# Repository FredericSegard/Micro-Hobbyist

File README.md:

# Micro-Hobbyist
 Frederic's electronics hobby repository

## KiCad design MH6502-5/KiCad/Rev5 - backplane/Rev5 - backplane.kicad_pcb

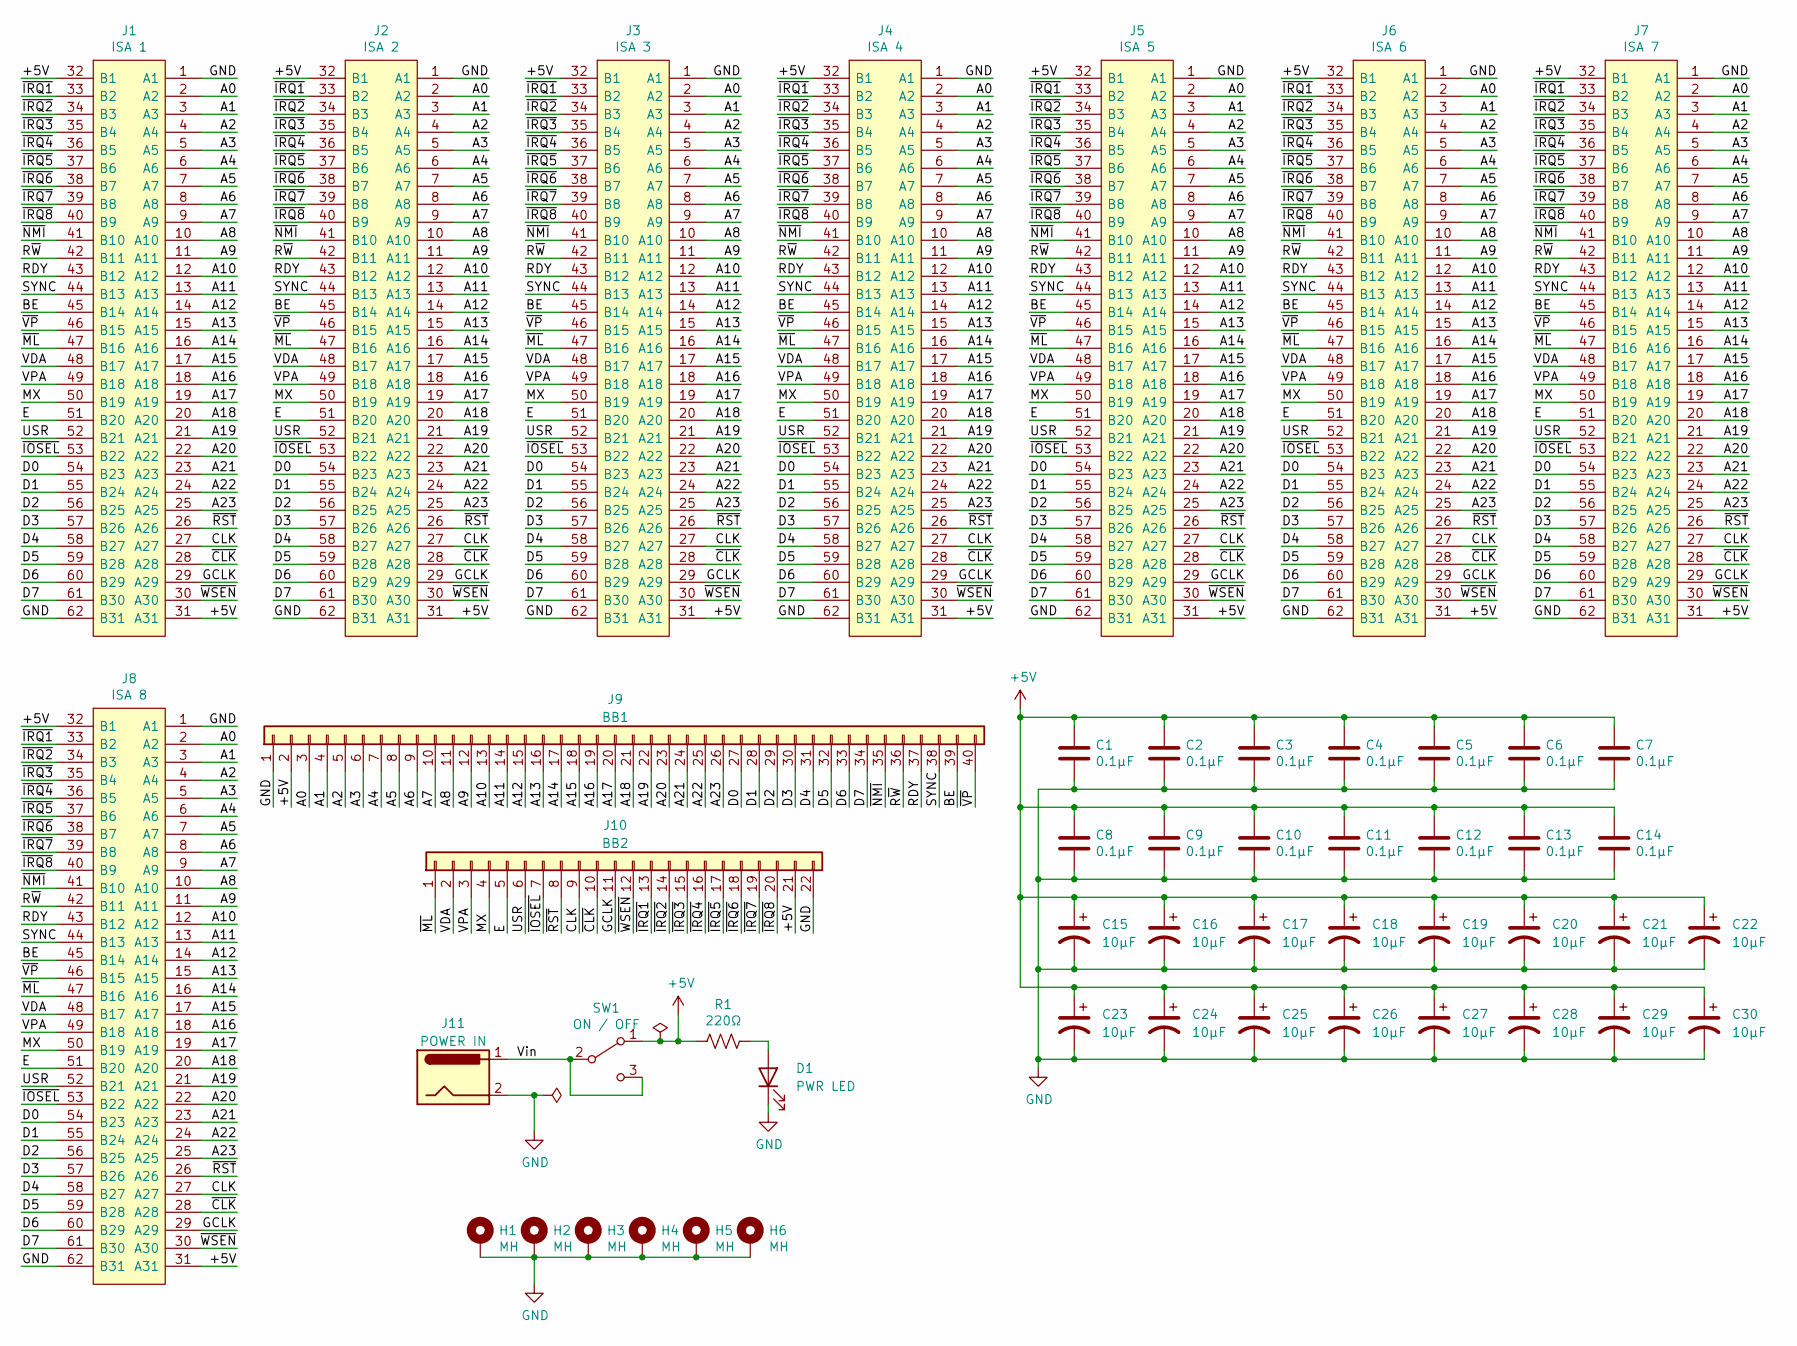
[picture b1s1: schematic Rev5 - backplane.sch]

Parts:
C1, C2, C3, C4, C5, C6, C7, C8, C9, C10, C11, C12, C13, C14: 0.1µF; C_Disc_D3.0mm_W2.0mm_P2.50mm
C15, C16, C17, C18, C19, C20, C21, C22, C23, C24, C25, C26, C27, C28, C29, C30: 10µF; CP_Radial_D6.3mm_P2.50mm
D1: PWR LED; LED_D3.0mm
H1, H2, H3, H4, H5, H6: MH; MountingHole_3.2mm_M3_Pad_Via
J1: ISA 1; ISA_Connector; Mouser Part Number 571-6-5530843-5
J2: ISA 2; ISA_Connector; Mouser Part Number 571-6-5530843-5
J3: ISA 3; ISA_Connector; Mouser Part Number 571-6-5530843-5
J4: ISA 4; ISA_Connector; Mouser Part Number 571-6-5530843-5
J5: ISA 5; ISA_Connector; Mouser Part Number 571-6-5530843-5
J6: ISA 6; ISA_Connector; Mouser Part Number 571-6-5530843-5
J7: ISA 7; ISA_Connector; Mouser Part Number 571-6-5530843-5
J8: ISA 8; ISA_Connector; Mouser Part Number 571-6-5530843-5
J9: BB1; PinHeader_1x40_P2.54mm_Vertical
J10: BB2; PinHeader_1x22_P2.54mm_Vertical
J11: POWER IN; BarrelJack_Horizontal
R1: 220Ω; R_Axial_DIN0207_L6.3mm_D2.5mm_P10.16mm_Horizontal
SW1: ON / OFF; Microswitch_3mm_spacing

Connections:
+5V: C1.1, C2.1, C3.1, C4.1, C5.1, C6.1, C7.1, C8.1, C9.1, C10.1, C11.1, C12.1, C13.1, C14.1, C15.1, C16.1, C17.1, C18.1, C19.1, C20.1, C21.1, C22.1, C23.1, C24.1, C25.1, C26.1, C27.1, C28.1, C29.1, C30.1, J1.31 (A31), J1.32 (B1), J2.31 (A31), J2.32 (B1), J3.31 (A31), J3.32 (B1), J4.31 (A31), J4.32 (B1), J5.31 (A31), J5.32 (B1), J6.31 (A31), J6.32 (B1), J7.31 (A31), J7.32 (B1), J8.31 (A31), J8.32 (B1), J9.2, J10.21, R1.2, SW1.1 (A)
/A0: J1.2 (A2), J2.2 (A2), J3.2 (A2), J4.2 (A2), J5.2 (A2), J6.2 (A2), J7.2 (A2), J8.2 (A2), J9.3
/A1: J1.3 (A3), J2.3 (A3), J3.3 (A3), J4.3 (A3), J5.3 (A3), J6.3 (A3), J7.3 (A3), J8.3 (A3), J9.4
/A2: J1.4 (A4), J2.4 (A4), J3.4 (A4), J4.4 (A4), J5.4 (A4), J6.4 (A4), J7.4 (A4), J8.4 (A4), J9.5
/A3: J1.5 (A5), J2.5 (A5), J3.5 (A5), J4.5 (A5), J5.5 (A5), J6.5 (A5), J7.5 (A5), J8.5 (A5), J9.6
/A4: J1.6 (A6), J2.6 (A6), J3.6 (A6), J4.6 (A6), J5.6 (A6), J6.6 (A6), J7.6 (A6), J8.6 (A6), J9.7
/A5: J1.7 (A7), J2.7 (A7), J3.7 (A7), J4.7 (A7), J5.7 (A7), J6.7 (A7), J7.7 (A7), J8.7 (A7), J9.8
/A6: J1.8 (A8), J2.8 (A8), J3.8 (A8), J4.8 (A8), J5.8 (A8), J6.8 (A8), J7.8 (A8), J8.8 (A8), J9.9
/A7: J1.9 (A9), J2.9 (A9), J3.9 (A9), J4.9 (A9), J5.9 (A9), J6.9 (A9), J7.9 (A9), J8.9 (A9), J9.10
/A8: J1.10 (A10), J2.10 (A10), J3.10 (A10), J4.10 (A10), J5.10 (A10), J6.10 (A10), J7.10 (A10), J8.10 (A10), J9.11
/A9: J1.11 (A11), J2.11 (A11), J3.11 (A11), J4.11 (A11), J5.11 (A11), J6.11 (A11), J7.11 (A11), J8.11 (A11), J9.12
/A10: J1.12 (A12), J2.12 (A12), J3.12 (A12), J4.12 (A12), J5.12 (A12), J6.12 (A12), J7.12 (A12), J8.12 (A12), J9.13
/A11: J1.13 (A13), J2.13 (A13), J3.13 (A13), J4.13 (A13), J5.13 (A13), J6.13 (A13), J7.13 (A13), J8.13 (A13), J9.14
/A12: J1.14 (A14), J2.14 (A14), J3.14 (A14), J4.14 (A14), J5.14 (A14), J6.14 (A14), J7.14 (A14), J8.14 (A14), J9.15
/A13: J1.15 (A15), J2.15 (A15), J3.15 (A15), J4.15 (A15), J5.15 (A15), J6.15 (A15), J7.15 (A15), J8.15 (A15), J9.16
/A14: J1.16 (A16), J2.16 (A16), J3.16 (A16), J4.16 (A16), J5.16 (A16), J6.16 (A16), J7.16 (A16), J8.16 (A16), J9.17
/A15: J1.17 (A17), J2.17 (A17), J3.17 (A17), J4.17 (A17), J5.17 (A17), J6.17 (A17), J7.17 (A17), J8.17 (A17), J9.18
/A16: J1.18 (A18), J2.18 (A18), J3.18 (A18), J4.18 (A18), J5.18 (A18), J6.18 (A18), J7.18 (A18), J8.18 (A18), J9.19
/A17: J1.19 (A19), J2.19 (A19), J3.19 (A19), J4.19 (A19), J5.19 (A19), J6.19 (A19), J7.19 (A19), J8.19 (A19), J9.20
/A18: J1.20 (A20), J2.20 (A20), J3.20 (A20), J4.20 (A20), J5.20 (A20), J6.20 (A20), J7.20 (A20), J8.20 (A20), J9.21
/A19: J1.21 (A21), J2.21 (A21), J3.21 (A21), J4.21 (A21), J5.21 (A21), J6.21 (A21), J7.21 (A21), J8.21 (A21), J9.22
/A20: J1.22 (A22), J2.22 (A22), J3.22 (A22), J4.22 (A22), J5.22 (A22), J6.22 (A22), J7.22 (A22), J8.22 (A22), J9.23
/A21: J1.23 (A23), J2.23 (A23), J3.23 (A23), J4.23 (A23), J5.23 (A23), J6.23 (A23), J7.23 (A23), J8.23 (A23), J9.24
/A22: J1.24 (A24), J2.24 (A24), J3.24 (A24), J4.24 (A24), J5.24 (A24), J6.24 (A24), J7.24 (A24), J8.24 (A24), J9.25
/A23: J1.25 (A25), J2.25 (A25), J3.25 (A25), J4.25 (A25), J5.25 (A25), J6.25 (A25), J7.25 (A25), J8.25 (A25), J9.26
/BE: J1.45 (B14), J2.45 (B14), J3.45 (B14), J4.45 (B14), J5.45 (B14), J6.45 (B14), J7.45 (B14), J8.45 (B14), J9.39
/CLK: J1.27 (A27), J2.27 (A27), J3.27 (A27), J4.27 (A27), J5.27 (A27), J6.27 (A27), J7.27 (A27), J8.27 (A27), J10.9
/D0: J1.54 (B23), J2.54 (B23), J3.54 (B23), J4.54 (B23), J5.54 (B23), J6.54 (B23), J7.54 (B23), J8.54 (B23), J9.27
/D1: J1.55 (B24), J2.55 (B24), J3.55 (B24), J4.55 (B24), J5.55 (B24), J6.55 (B24), J7.55 (B24), J8.55 (B24), J9.28
/D2: J1.56 (B25), J2.56 (B25), J3.56 (B25), J4.56 (B25), J5.56 (B25), J6.56 (B25), J7.56 (B25), J8.56 (B25), J9.29
/D3: J1.57 (B26), J2.57 (B26), J3.57 (B26), J4.57 (B26), J5.57 (B26), J6.57 (B26), J7.57 (B26), J8.57 (B26), J9.30
/D4: J1.58 (B27), J2.58 (B27), J3.58 (B27), J4.58 (B27), J5.58 (B27), J6.58 (B27), J7.58 (B27), J8.58 (B27), J9.31
/D5: J1.59 (B28), J2.59 (B28), J3.59 (B28), J4.59 (B28), J5.59 (B28), J6.59 (B28), J7.59 (B28), J8.59 (B28), J9.32
/D6: J1.60 (B29), J2.60 (B29), J3.60 (B29), J4.60 (B29), J5.60 (B29), J6.60 (B29), J7.60 (B29), J8.60 (B29), J9.33
/D7: J1.61 (B30), J2.61 (B30), J3.61 (B30), J4.61 (B30), J5.61 (B30), J6.61 (B30), J7.61 (B30), J8.61 (B30), J9.34
/E: J1.51 (B20), J2.51 (B20), J3.51 (B20), J4.51 (B20), J5.51 (B20), J6.51 (B20), J7.51 (B20), J8.51 (B20), J10.5
/GCLK: J1.29 (A29), J2.29 (A29), J3.29 (A29), J4.29 (A29), J5.29 (A29), J6.29 (A29), J7.29 (A29), J8.29 (A29), J10.11
/MX: J1.50 (B19), J2.50 (B19), J3.50 (B19), J4.50 (B19), J5.50 (B19), J6.50 (B19), J7.50 (B19), J8.50 (B19), J10.4
/RDY: J1.43 (B12), J2.43 (B12), J3.43 (B12), J4.43 (B12), J5.43 (B12), J6.43 (B12), J7.43 (B12), J8.43 (B12), J9.37
/R~W: J1.42 (B11), J2.42 (B11), J3.42 (B11), J4.42 (B11), J5.42 (B11), J6.42 (B11), J7.42 (B11), J8.42 (B11), J9.36
/SYNC: J1.44 (B13), J2.44 (B13), J3.44 (B13), J4.44 (B13), J5.44 (B13), J6.44 (B13), J7.44 (B13), J8.44 (B13), J9.38
/USR: J1.52 (B21), J2.52 (B21), J3.52 (B21), J4.52 (B21), J5.52 (B21), J6.52 (B21), J7.52 (B21), J8.52 (B21), J10.6
/VDA: J1.48 (B17), J2.48 (B17), J3.48 (B17), J4.48 (B17), J5.48 (B17), J6.48 (B17), J7.48 (B17), J8.48 (B17), J10.2
/VPA: J1.49 (B18), J2.49 (B18), J3.49 (B18), J4.49 (B18), J5.49 (B18), J6.49 (B18), J7.49 (B18), J8.49 (B18), J10.3
/Vin: J11.1, SW1.2 (B), SW1.3 (C)
/~CLK: J1.28 (A28), J2.28 (A28), J3.28 (A28), J4.28 (A28), J5.28 (A28), J6.28 (A28), J7.28 (A28), J8.28 (A28), J10.10
/~IOSEL: J1.53 (B22), J2.53 (B22), J3.53 (B22), J4.53 (B22), J5.53 (B22), J6.53 (B22), J7.53 (B22), J8.53 (B22), J10.7
/~IRQ1: J1.33 (B2), J2.33 (B2), J3.33 (B2), J4.33 (B2), J5.33 (B2), J6.33 (B2), J7.33 (B2), J8.33 (B2), J10.13
/~IRQ2: J1.34 (B3), J2.34 (B3), J3.34 (B3), J4.34 (B3), J5.34 (B3), J6.34 (B3), J7.34 (B3), J8.34 (B3), J10.14
/~IRQ3: J1.35 (B4), J2.35 (B4), J3.35 (B4), J4.35 (B4), J5.35 (B4), J6.35 (B4), J7.35 (B4), J8.35 (B4), J10.15
/~IRQ4: J1.36 (B5), J2.36 (B5), J3.36 (B5), J4.36 (B5), J5.36 (B5), J6.36 (B5), J7.36 (B5), J8.36 (B5), J10.16
/~IRQ5: J1.37 (B6), J2.37 (B6), J3.37 (B6), J4.37 (B6), J5.37 (B6), J6.37 (B6), J7.37 (B6), J8.37 (B6), J10.17
/~IRQ6: J1.38 (B7), J2.38 (B7), J3.38 (B7), J4.38 (B7), J5.38 (B7), J6.38 (B7), J7.38 (B7), J8.38 (B7), J10.18
/~IRQ7: J1.39 (B8), J2.39 (B8), J3.39 (B8), J4.39 (B8), J5.39 (B8), J6.39 (B8), J7.39 (B8), J8.39 (B8), J10.19
/~IRQ8: J1.40 (B9), J2.40 (B9), J3.40 (B9), J4.40 (B9), J5.40 (B9), J6.40 (B9), J7.40 (B9), J8.40 (B9), J10.20
/~ML: J1.47 (B16), J2.47 (B16), J3.47 (B16), J4.47 (B16), J5.47 (B16), J6.47 (B16), J7.47 (B16), J8.47 (B16), J10.1
/~NMI: J1.41 (B10), J2.41 (B10), J3.41 (B10), J4.41 (B10), J5.41 (B10), J6.41 (B10), J7.41 (B10), J8.41 (B10), J9.35
/~RST: J1.26 (A26), J2.26 (A26), J3.26 (A26), J4.26 (A26), J5.26 (A26), J6.26 (A26), J7.26 (A26), J8.26 (A26), J10.8
/~VP: J1.46 (B15), J2.46 (B15), J3.46 (B15), J4.46 (B15), J5.46 (B15), J6.46 (B15), J7.46 (B15), J8.46 (B15), J9.40
/~WSEN: J1.30 (A30), J2.30 (A30), J3.30 (A30), J4.30 (A30), J5.30 (A30), J6.30 (A30), J7.30 (A30), J8.30 (A30), J10.12
GND: C1.2, C2.2, C3.2, C4.2, C5.2, C6.2, C7.2, C8.2, C9.2, C10.2, C11.2, C12.2, C13.2, C14.2, C15.2, C16.2, C17.2, C18.2, C19.2, C20.2, C21.2, C22.2, C23.2, C24.2, C25.2, C26.2, C27.2, C28.2, C29.2, C30.2, D1.1 (K), H1.1, H2.1, H3.1, H4.1, H5.1, H6.1, J1.1 (A1), J1.62 (B31), J2.1 (A1), J2.62 (B31), J3.1 (A1), J3.62 (B31), J4.1 (A1), J4.62 (B31), J5.1 (A1), J5.62 (B31), J6.1 (A1), J6.62 (B31), J7.1 (A1), J7.62 (B31), J8.1 (A1), J8.62 (B31), J9.1, J10.22, J11.2
unnamed: D1.2 (A), R1.1

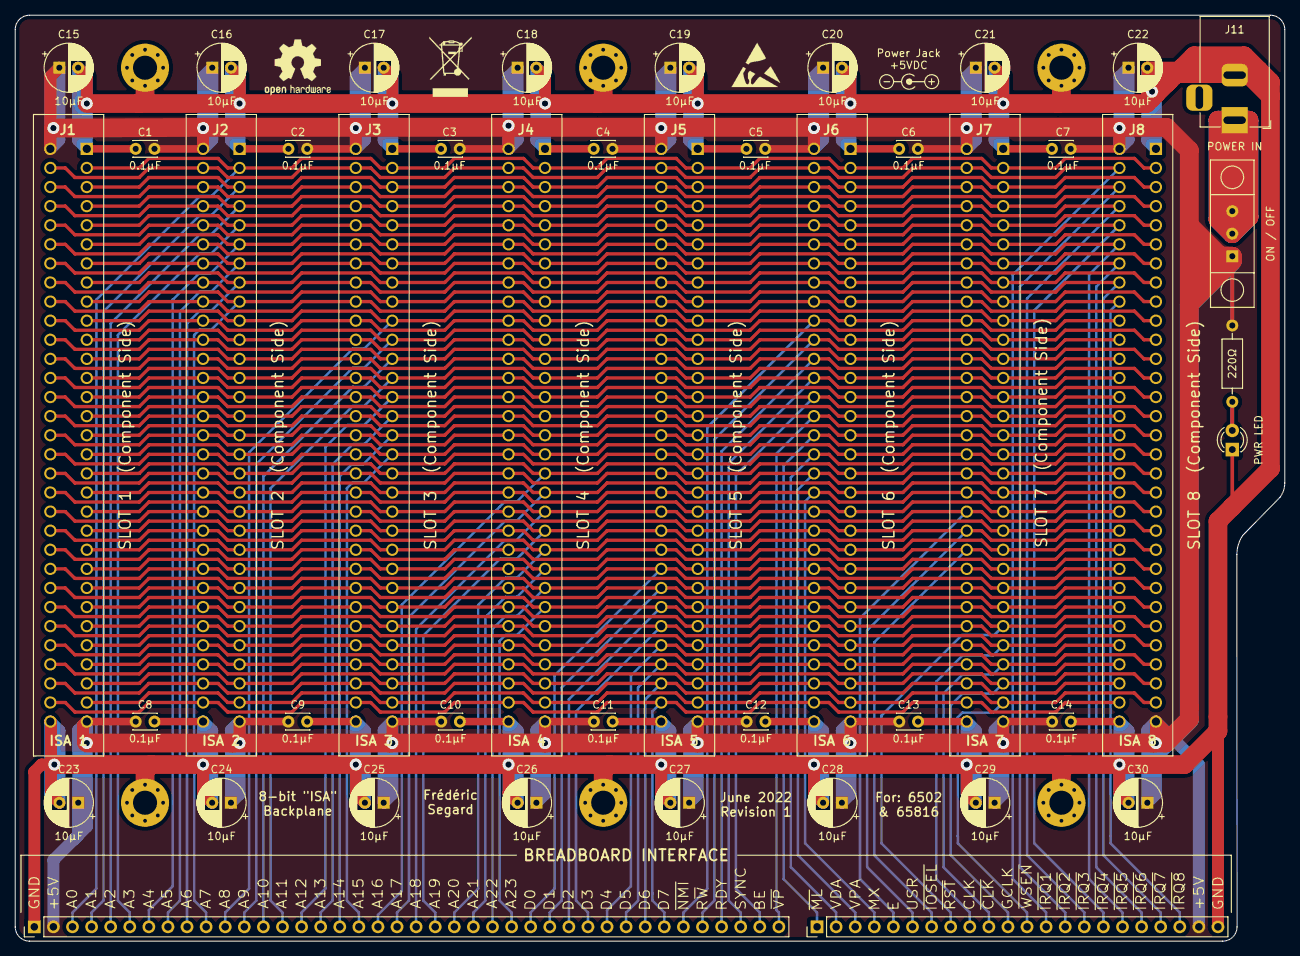
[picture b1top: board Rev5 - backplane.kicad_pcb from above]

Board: 4 copper layers, 168.9 x 123.2 mm, 50 parts (0 on the bottom side), 62 nets.

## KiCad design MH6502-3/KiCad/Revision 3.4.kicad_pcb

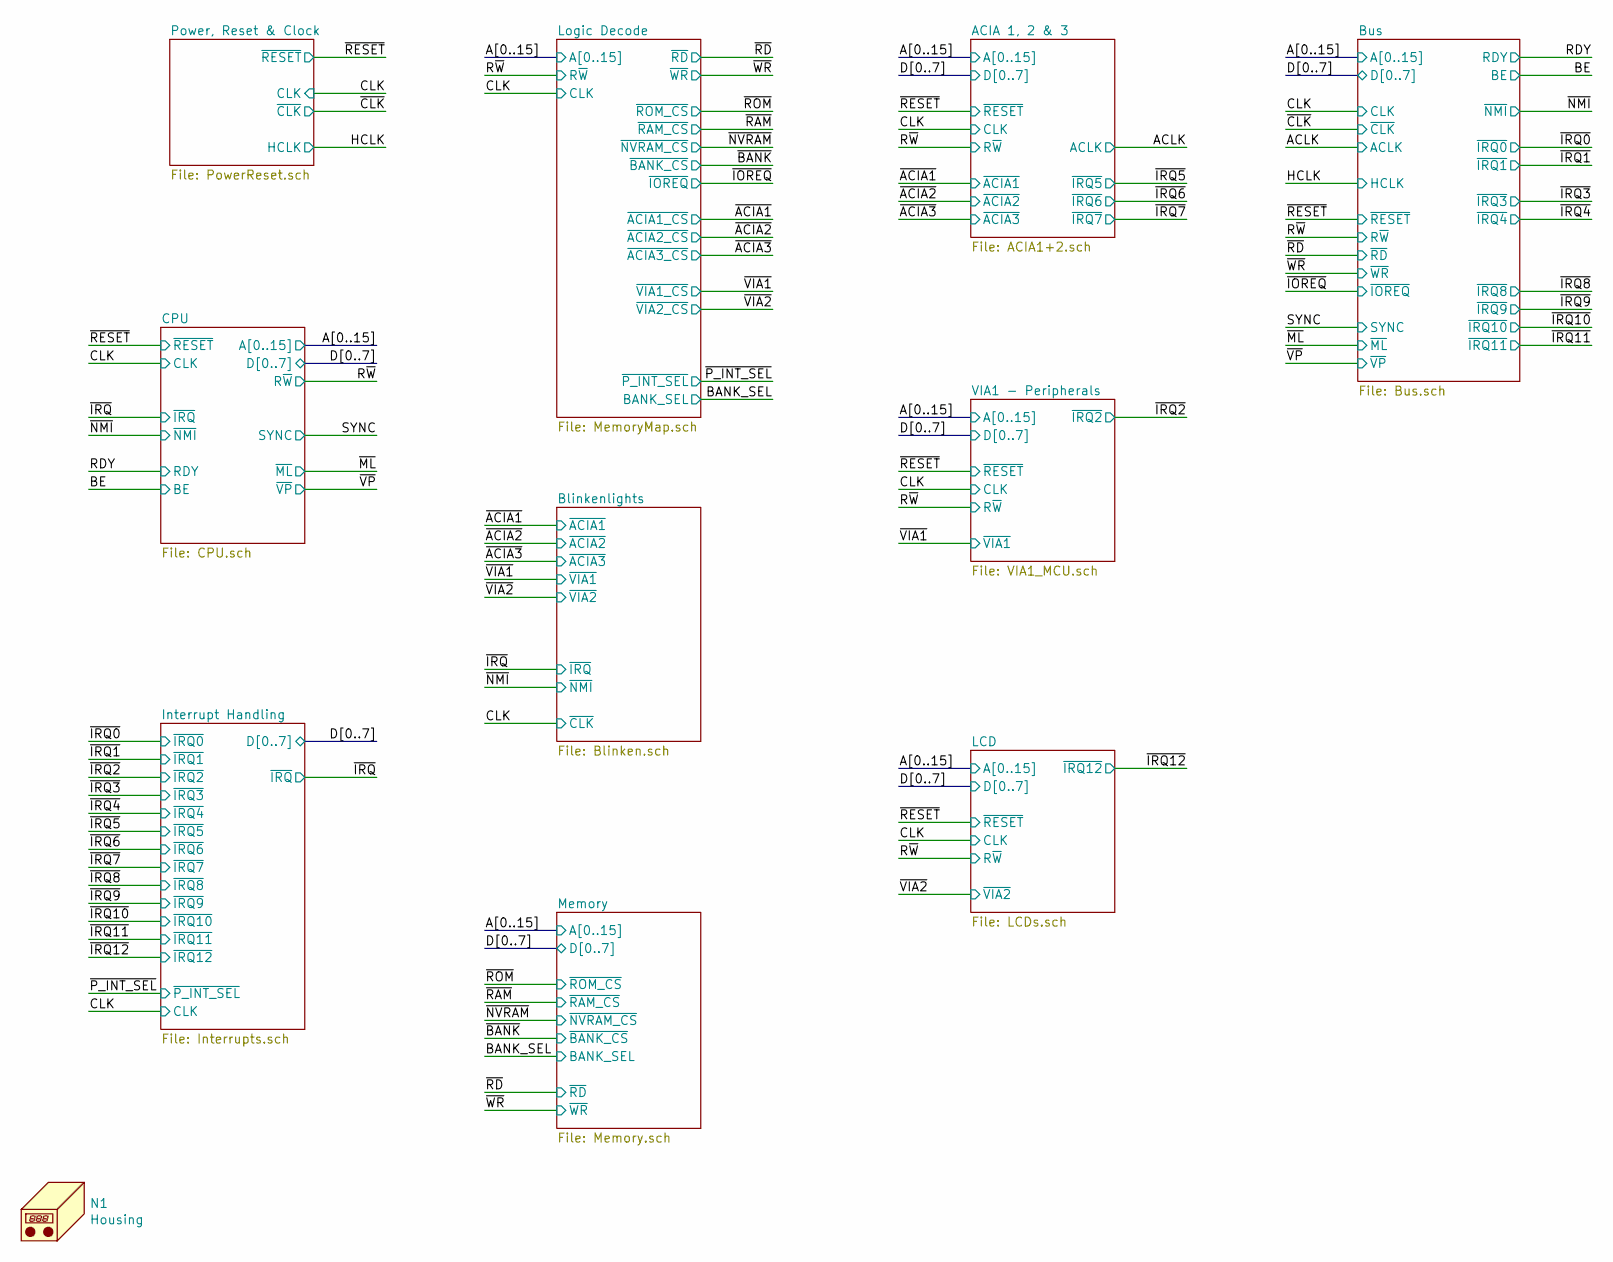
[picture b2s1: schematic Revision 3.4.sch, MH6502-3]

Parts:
N1: Housing; 18877_Housing

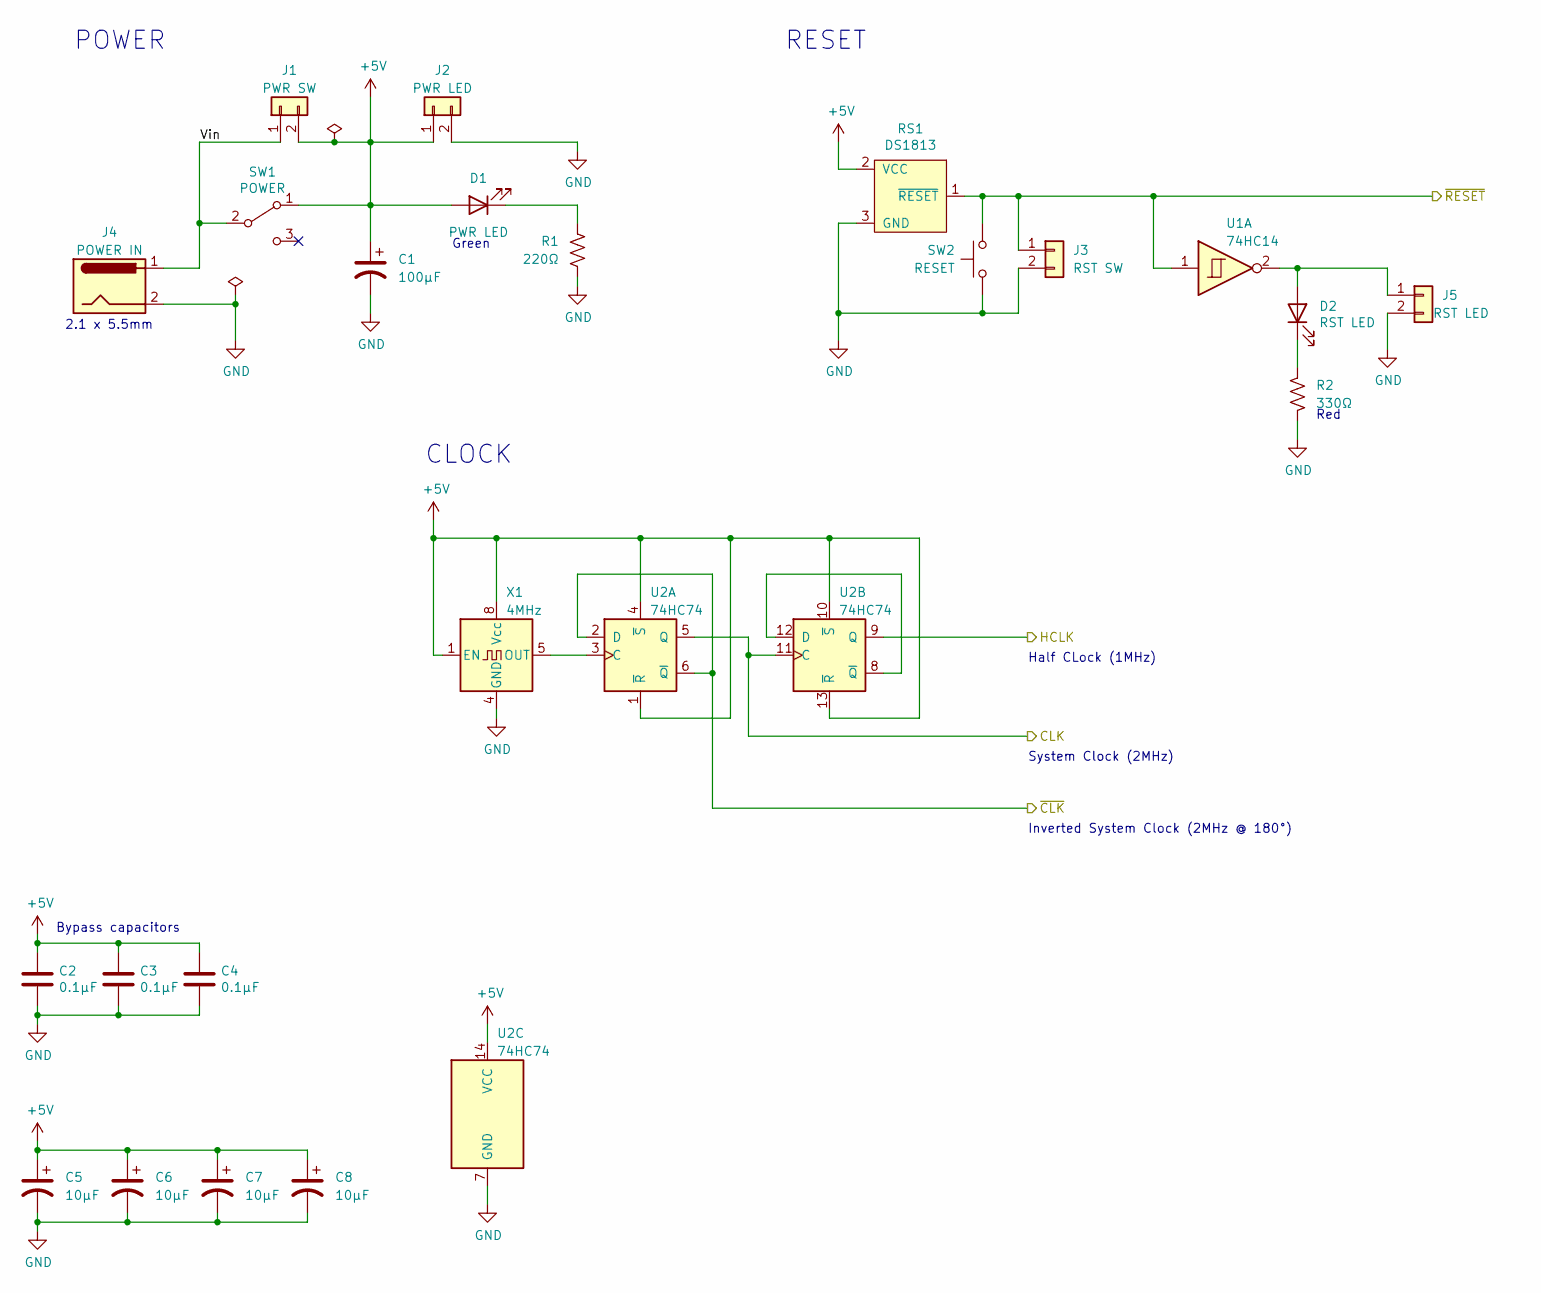
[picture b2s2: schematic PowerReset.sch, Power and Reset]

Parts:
C1: 100µF; CP_Radial_D8.0mm_P3.80mm
C2, C3, C4: 0.1µF; C_Disc_D3.0mm_W1.6mm_P2.50mm
C5, C6, C7, C8: 10µF; CP_Radial_D6.3mm_P2.50mm
D1: PWR LED; LED_D3.0mm
D2: RST LED; LED_D3.0mm
J1: PWR SW; PinHeader_1x02_P2.54mm_Vertical
J2: PWR LED; PinHeader_1x02_P2.54mm_Vertical
J3: RST SW; PinHeader_1x02_P2.54mm_Vertical
J4: POWER IN; BarrelJack_Horizontal
J5: RST LED; PinHeader_1x02_P2.54mm_Vertical
R1: 220Ω; R_Axial_DIN0207_L6.3mm_D2.5mm_P10.16mm_Horizontal
R2: 330Ω; R_Axial_DIN0207_L6.3mm_D2.5mm_P10.16mm_Horizontal
RS1: DS1813; TO-92L_Inline_Wide
SW1: POWER; Microswitch_3mm_spacing
SW2: RESET; SW_PUSH_6mm
U1: 74HC14; DIP-14_W7.62mm_Socket
U2: 74HC74; DIP-14_W7.62mm_Socket
X1: 4MHz; Oscillator_DIP-8

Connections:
+5V: C1.1, C2.1, C3.1, C4.1, C5.1, C6.1, C7.1, C8.1, D1.2 (A), J1.2, J2.1, RS1.2 (VCC), SW1.1 (A), U2.1 (~R), U2.4 (~S), U2.10 (~S), U2.13 (~R), U2.14 (VCC), X1.1 (EN), X1.8 (Vcc); also elsewhere on the board
/CLK: U2.5 (Q), U2.11 (C); also elsewhere on the board
/HCLK: U2.9 (Q); also elsewhere on the board
/Power, Reset & Clock/Vin: J1.1, J4.1, SW1.2 (B)
/~CLK: U2.2 (D), U2.6 (~Q); also elsewhere on the board
/~RESET: J3.1, RS1.1 (~RESET), SW2.1, U1.1; also elsewhere on the board
GND: C1.2, C2.2, C3.2, C4.2, C5.2, C6.2, C7.2, C8.2, J2.2, J3.2, J4.2, J5.2, R1.1, R2.1, RS1.3 (GND), SW2.2, U2.7 (GND), X1.4 (GND); also elsewhere on the board
unnamed: D1.1 (K), R1.2
unnamed: D2.1 (K), R2.2
unnamed: D2.2 (A), J5.1, U1.2
unnamed: U2.3 (C), X1.5 (OUT)
unnamed: U2.8 (~Q), U2.12 (D)

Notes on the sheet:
2.1 x 5.5mm
Green
Bypass capacitors
Red
POWER
CLOCK
RESET
Half CLock (1MHz)
Inverted System Clock (2MHz @ 180°)
System Clock (2MHz)

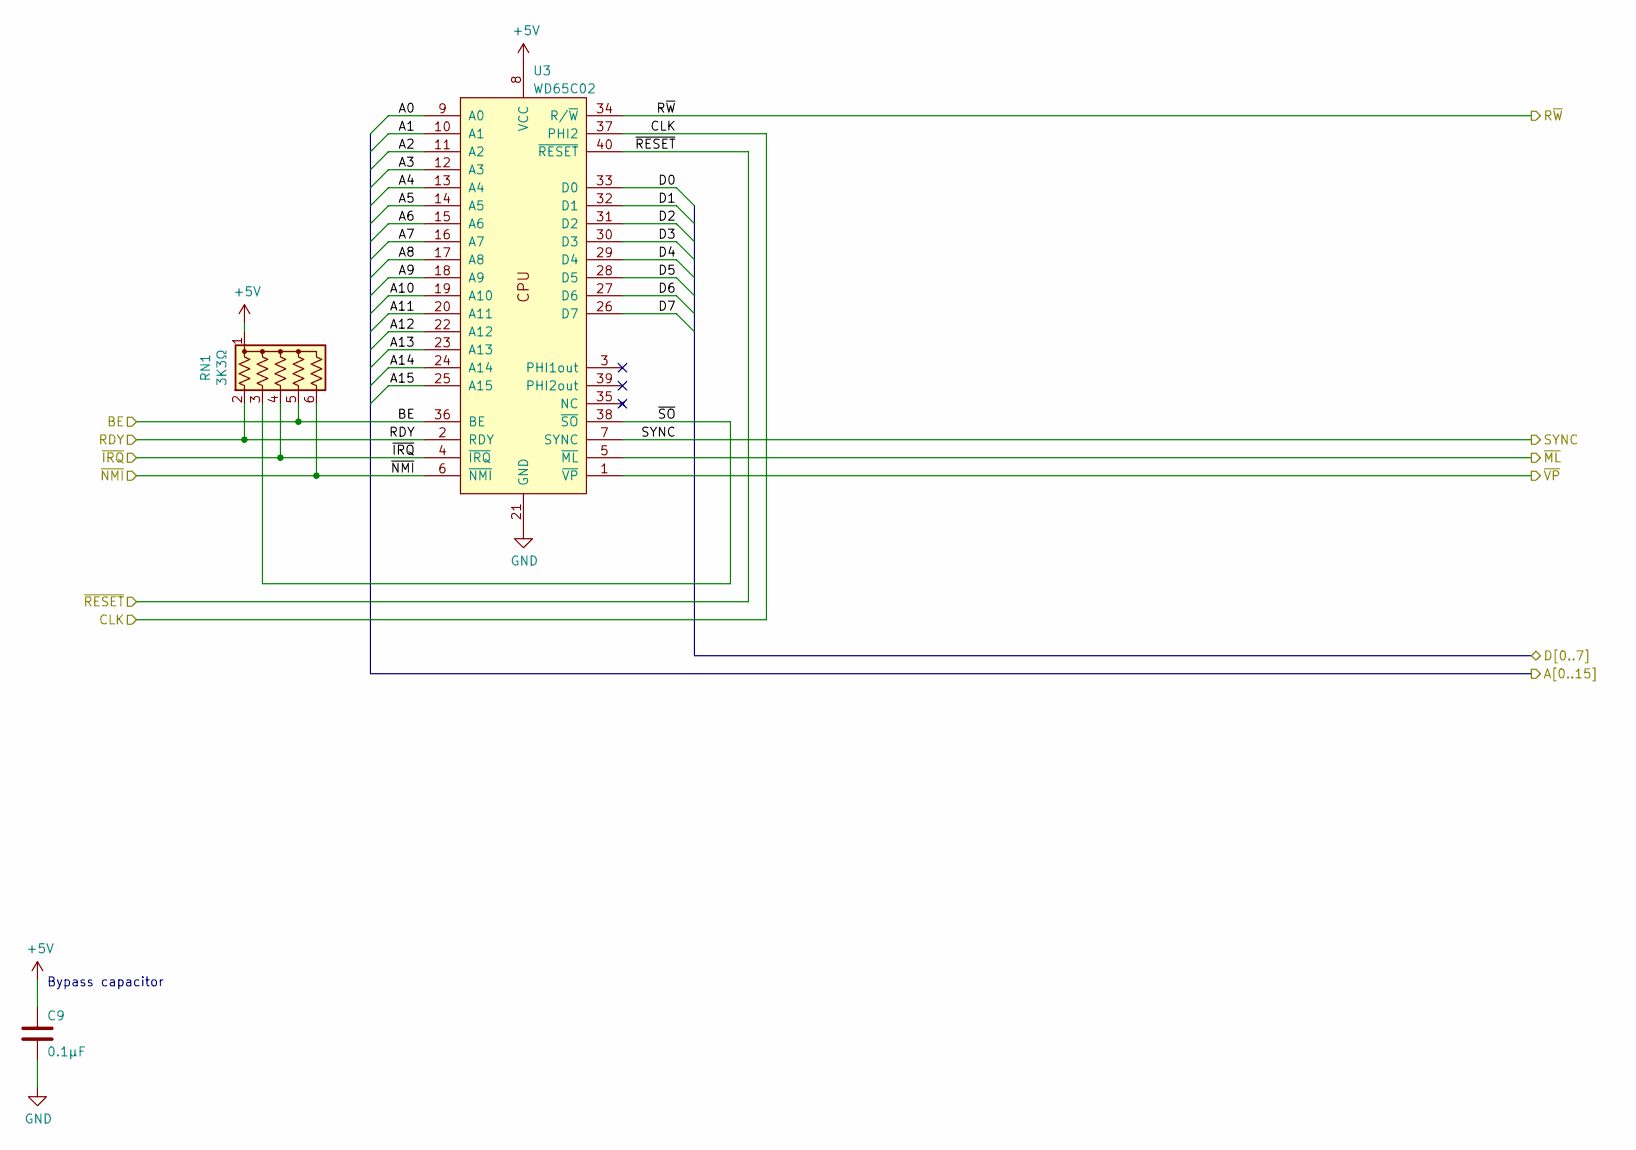
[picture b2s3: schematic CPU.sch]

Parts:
C9: 0.1µF; C_Disc_D3.0mm_W1.6mm_P2.50mm
RN1: 3K3Ω; R_Array_SIP6
U3: WD65C02; DIP-40_W15.24mm_Socket

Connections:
+5V: C9.1, RN1.1 (common), U3.8 (VCC); also elsewhere on the board
/ACIA 1, 2 & 3/A0: U3.9 (A0); also elsewhere on the board
/ACIA 1, 2 & 3/A1: U3.10 (A1); also elsewhere on the board
/ACIA 1, 2 & 3/D0: U3.33 (D0); also elsewhere on the board
/ACIA 1, 2 & 3/D1: U3.32 (D1); also elsewhere on the board
/ACIA 1, 2 & 3/D2: U3.31 (D2); also elsewhere on the board
/ACIA 1, 2 & 3/D3: U3.30 (D3); also elsewhere on the board
/ACIA 1, 2 & 3/D4: U3.29 (D4); also elsewhere on the board
/ACIA 1, 2 & 3/D5: U3.28 (D5); also elsewhere on the board
/ACIA 1, 2 & 3/D6: U3.27 (D6); also elsewhere on the board
/ACIA 1, 2 & 3/D7: U3.26 (D7); also elsewhere on the board
/BE: RN1.5 (R4), U3.36 (BE); also elsewhere on the board
/Bus/A2: U3.11 (A2); also elsewhere on the board
/Bus/A3: U3.12 (A3); also elsewhere on the board
/Bus/A4: U3.13 (A4); also elsewhere on the board
/Bus/A5: U3.14 (A5); also elsewhere on the board
/Bus/A6: U3.15 (A6); also elsewhere on the board
/Bus/A7: U3.16 (A7); also elsewhere on the board
/Bus/A8: U3.17 (A8); also elsewhere on the board
/Bus/A9: U3.18 (A9); also elsewhere on the board
/Bus/A10: U3.19 (A10); also elsewhere on the board
/Bus/A11: U3.20 (A11); also elsewhere on the board
/Bus/A12: U3.22 (A12); also elsewhere on the board
/Bus/A13: U3.23 (A13); also elsewhere on the board
/Bus/A14: U3.24 (A14); also elsewhere on the board
/Bus/A15: U3.25 (A15); also elsewhere on the board
/CLK: U3.37 (PHI2); also elsewhere on the board
/CPU/~SO: RN1.3 (R2), U3.38 (~SO)
/RDY: RN1.2 (R1), U3.2 (RDY); also elsewhere on the board
/R~W: U3.34 (R/~W); also elsewhere on the board
/SYNC: U3.7 (SYNC); also elsewhere on the board
/~IRQ: RN1.4 (R3), U3.4 (~IRQ); also elsewhere on the board
/~ML: U3.5 (~ML); also elsewhere on the board
/~NMI: RN1.6 (R5), U3.6 (~NMI); also elsewhere on the board
/~RESET: U3.40 (~RESET); also elsewhere on the board
/~VP: U3.1 (~VP); also elsewhere on the board
GND: C9.2, U3.21 (GND); also elsewhere on the board

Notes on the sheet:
Bypass capacitor

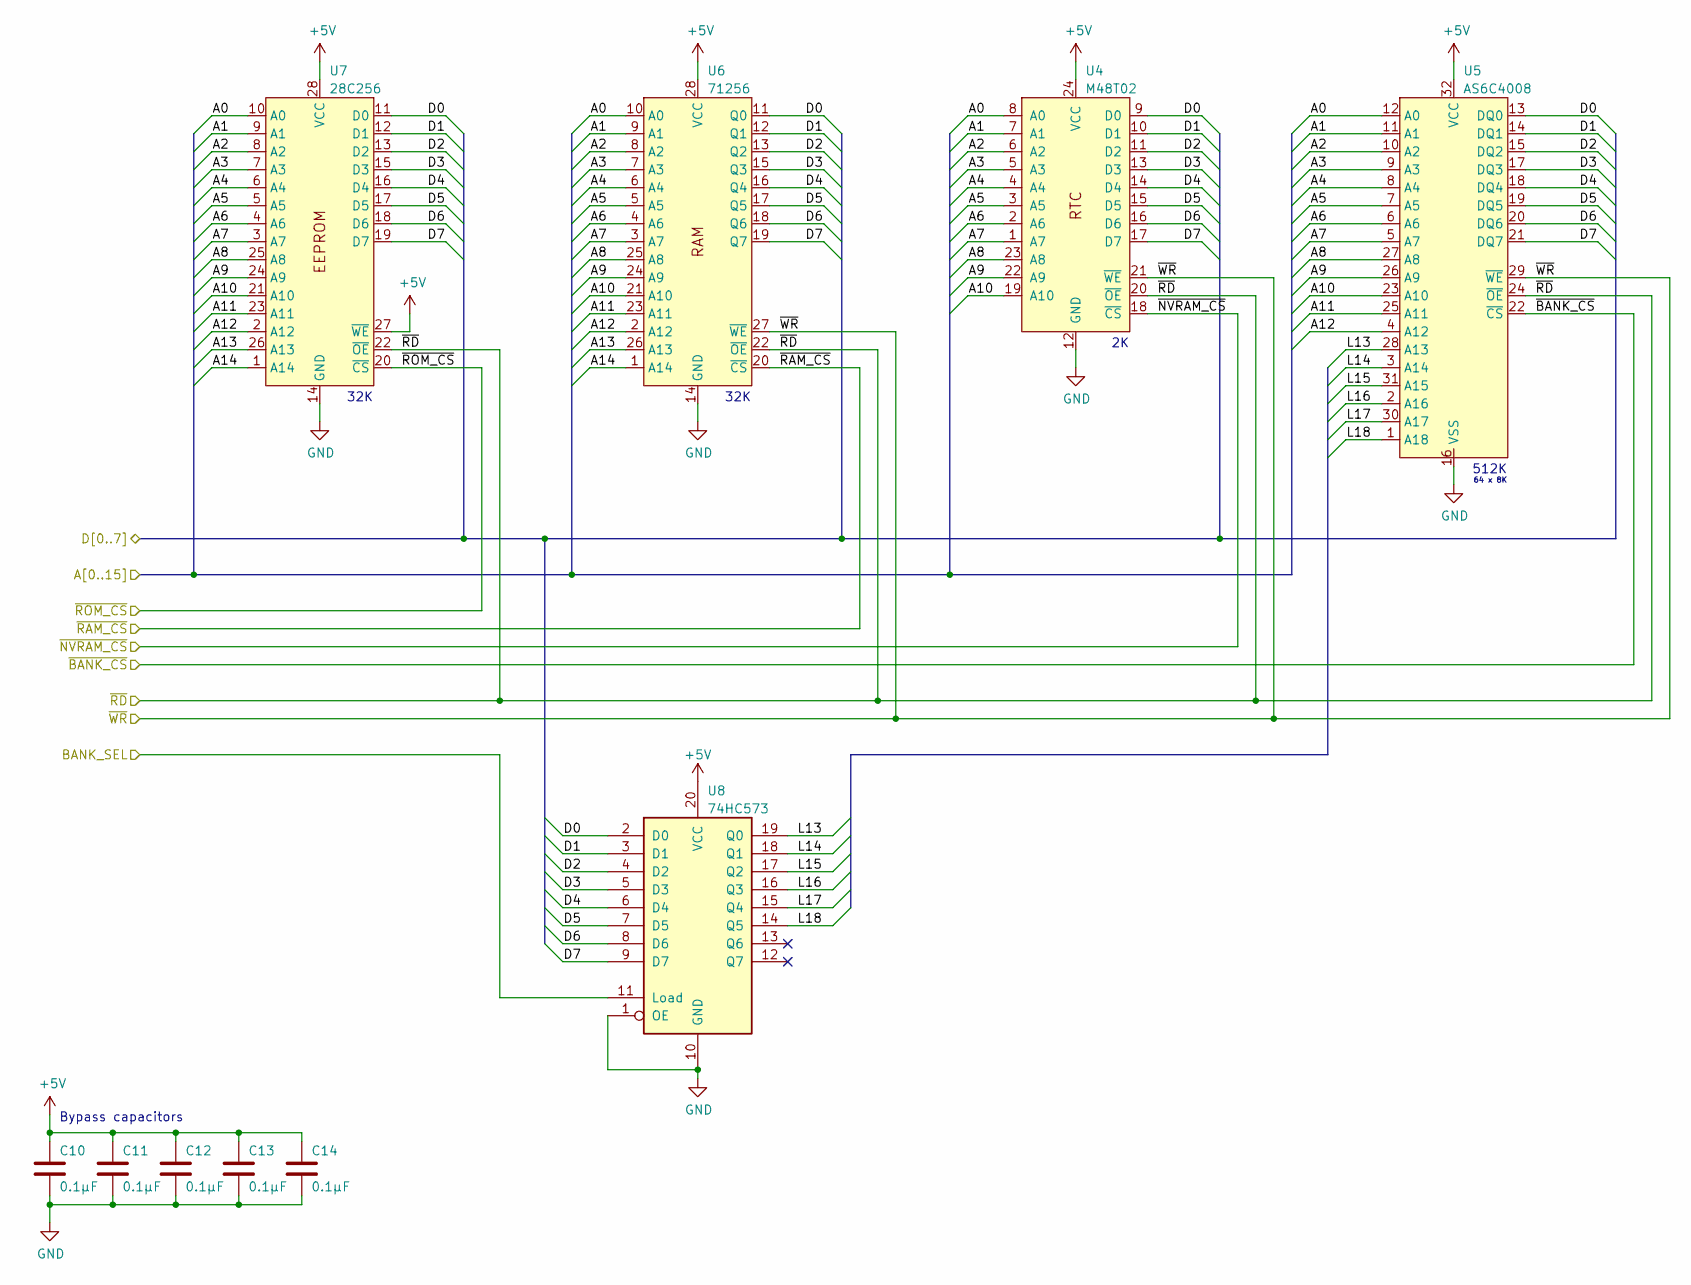
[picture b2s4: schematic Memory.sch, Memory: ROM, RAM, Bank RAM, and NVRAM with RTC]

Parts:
C10, C11, C12, C13, C14: 0.1µF; C_Disc_D3.0mm_W1.6mm_P2.50mm
U4: M48T02; DIP-24_W15.24mm_Socket
U5: AS6C4008; DIP-32_W15.24mm_Socket
U6: 71256; DIP-28_W7.62mm_Socket
U7: 28C256; ZIF-28
U8: 74HC573; DIP-20_W7.62mm_Socket

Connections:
+5V: C10.1, C11.1, C12.1, C13.1, C14.1, U4.24 (VCC), U5.32 (VCC), U6.28 (VCC), U7.27 (~WE), U7.28 (VCC), U8.20 (VCC); also elsewhere on the board
/ACIA 1, 2 & 3/A0: U4.8 (A0), U5.12 (A0), U6.10 (A0), U7.10 (A0); also elsewhere on the board
/ACIA 1, 2 & 3/A1: U4.7 (A1), U5.11 (A1), U6.9 (A1), U7.9 (A1); also elsewhere on the board
/ACIA 1, 2 & 3/D0: U4.9 (D0), U5.13 (DQ0), U6.11 (Q0), U7.11 (D0), U8.2 (D0); also elsewhere on the board
/ACIA 1, 2 & 3/D1: U4.10 (D1), U5.14 (DQ1), U6.12 (Q1), U7.12 (D1), U8.3 (D1); also elsewhere on the board
/ACIA 1, 2 & 3/D2: U4.11 (D2), U5.15 (DQ2), U6.13 (Q2), U7.13 (D2), U8.4 (D2); also elsewhere on the board
/ACIA 1, 2 & 3/D3: U4.13 (D3), U5.17 (DQ3), U6.15 (Q3), U7.15 (D3), U8.5 (D3); also elsewhere on the board
/ACIA 1, 2 & 3/D4: U4.14 (D4), U5.18 (DQ4), U6.16 (Q4), U7.16 (D4), U8.6 (D4); also elsewhere on the board
/ACIA 1, 2 & 3/D5: U4.15 (D5), U5.19 (DQ5), U6.17 (Q5), U7.17 (D5), U8.7 (D5); also elsewhere on the board
/ACIA 1, 2 & 3/D6: U4.16 (D6), U5.20 (DQ6), U6.18 (Q6), U7.18 (D6), U8.8 (D6); also elsewhere on the board
/ACIA 1, 2 & 3/D7: U4.17 (D7), U5.21 (DQ7), U6.19 (Q7), U7.19 (D7), U8.9 (D7); also elsewhere on the board
/BANK_SEL: U8.11 (Load); also elsewhere on the board
/Bus/A2: U4.6 (A2), U5.10 (A2), U6.8 (A2), U7.8 (A2); also elsewhere on the board
/Bus/A3: U4.5 (A3), U5.9 (A3), U6.7 (A3), U7.7 (A3); also elsewhere on the board
/Bus/A4: U4.4 (A4), U5.8 (A4), U6.6 (A4), U7.6 (A4); also elsewhere on the board
/Bus/A5: U4.3 (A5), U5.7 (A5), U6.5 (A5), U7.5 (A5); also elsewhere on the board
/Bus/A6: U4.2 (A6), U5.6 (A6), U6.4 (A6), U7.4 (A6); also elsewhere on the board
/Bus/A7: U4.1 (A7), U5.5 (A7), U6.3 (A7), U7.3 (A7); also elsewhere on the board
/Bus/A8: U4.23 (A8), U5.27 (A8), U6.25 (A8), U7.25 (A8); also elsewhere on the board
/Bus/A9: U4.22 (A9), U5.26 (A9), U6.24 (A9), U7.24 (A9); also elsewhere on the board
/Bus/A10: U4.19 (A10), U5.23 (A10), U6.21 (A10), U7.21 (A10); also elsewhere on the board
/Bus/A11: U5.25 (A11), U6.23 (A11), U7.23 (A11); also elsewhere on the board
/Bus/A12: U5.4 (A12), U6.2 (A12), U7.2 (A12); also elsewhere on the board
/Bus/A13: U6.26 (A13), U7.26 (A13); also elsewhere on the board
/Bus/A14: U6.1 (A14), U7.1 (A14); also elsewhere on the board
/Memory/L13: U5.28 (A13), U8.19 (Q0)
/Memory/L14: U5.3 (A14), U8.18 (Q1)
/Memory/L15: U5.31 (A15), U8.17 (Q2)
/Memory/L16: U5.2 (A16), U8.16 (Q3)
/Memory/L17: U5.30 (A17), U8.15 (Q4)
/Memory/L18: U5.1 (A18), U8.14 (Q5)
/~BANK: U5.22 (~CS); also elsewhere on the board
/~NVRAM: U4.18 (~CS); also elsewhere on the board
/~RAM: U6.20 (~CS); also elsewhere on the board
/~RD: U4.20 (~OE), U5.24 (~OE), U6.22 (~OE), U7.22 (~OE); also elsewhere on the board
/~ROM: U7.20 (~CS); also elsewhere on the board
/~WR: U4.21 (~WE), U5.29 (~WE), U6.27 (~WE); also elsewhere on the board
GND: C10.2, C11.2, C12.2, C13.2, C14.2, U4.12 (GND), U5.16 (VSS), U6.14 (GND), U7.14 (GND), U8.1 (OE), U8.10 (GND); also elsewhere on the board

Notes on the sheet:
32K
Bypass capacitors
512K
64 x 8K
